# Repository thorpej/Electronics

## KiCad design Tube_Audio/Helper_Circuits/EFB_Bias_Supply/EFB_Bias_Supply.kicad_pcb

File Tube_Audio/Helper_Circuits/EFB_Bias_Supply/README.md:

# EFB(tm) Bias Supply

## EFB(tm) - Enhanced Fixed Bias(tm)

This is a negative bias supply and regulator circuit for use in push-pull Class AB1 fixed bias output
stages of a tube power amplifier.  It is an adaptation of the "EFB II" circuit, developed by
David Gillespie and documented in this thread on AudioKarma: [Improving the Fisher SA-100 with EFB II](http://audiokarma.org/forums/index.php?threads/improving-the-fisher-sa-100-with-efb-ii.476431/).
The idea behind "EFB II" is to maintain the optimum relationship between the negative bias
voltage applied to the tube grids and a reference voltage (the screen supply voltage in a pentode
output stage; the plate supply voltage in an ultra-linear or triode output stage) at any power output
conditions, up to the maximum power the output stage is capable of delivering.  When the
reference voltage sags during, for example, maximum output conditions, the bias voltage will be
reduced (made less negative) proportionally to the change in reference voltage in order to maintain
the desired operating point (avoid an over-bias condition).  This leads to improved performance
(higher power output with less distortion) while also frequently leading to improved tube life
(because the output stage does not need to be under-biased in order to achieve maximum
performance under maximum power conditions).

David's circuit is very clever: a current is passed from the voltage reference through a sense
resistor.  This current produces a voltage drop across another resistor (or resistor network).
This voltage drop is inverted and buffered by a pair of PNP transistors that drive the bias
adjustment and balance network that is tied to the output tube grids.  Any change in the reference
voltage (up or down) results in a change in the sense current, resulting in a proportional change
in the voltage drop across the resistor(s) that set the base bias voltage.

This board is intended to more or less fully encapsulate a bias supply; it contains a half-wave
rectifier and two filter capacitors, in addition to the "EFB II" circuitry.  To use it, simply determine
what your "raw bias voltage" should be, plug in a few values into a handy spreadsheet I've
provided, and then install the calculated components onto the board, *et viola*!  It's tailored for
your particular application.

## Parts you'll need to build your EFB(tm) Bias Supply board

There are a few specific components required to properly assemble your EFB(tm) Bias Supply board.

* A PCB-mounted 50K linear trim pot, TE 409HA503M or equivalent.
* A rectangular radial .22µF (220nF) 50V film capacitor, Kemet SMR5224J50J02L16.5 or equivalent.
* A radial 100µF 250V electrolytic capacitor, 7.5mm lead spacing, up to 16.0mm diameter, Panasonic EEU-ED2E101 or equivalent.
* A radial 47µF 250V electrolytic capacitor, 5.0mm lead spacing, up to 12.5mm diameter, Panasonic EEU-ED2E470 or equivalent.

(All of the above mentioned parts are available from Mouser.)

You will also need:

* 2x 1N4007 diodes.
* 2x KSA1013 or equivalent PNP transistors in TO-92 packages, ECB pin configuration.

...plus a handful of resistors (see the following section about configuring the board), and optional
screw terminal blocks (you can opt to use flying leads if you wish).

Please note that the KSA1013 has a maximum Vce rating of -160V.  If your application requires
a bias voltage in excess of -70V, the KSA1013 may not be suitable.  If you can find another
PNP transistor with a suitable Vce rating in a TO-92 package with an ECB pin configuration, you
should be able to substitute it.  If there's sufficient interest, I could spin another revision of the
board that uses a different TO-92 pin configuration if a suitable high-voltage ECB transistor
proves elusive.  I chose the KSA1013 because that's what David used originally and the price
is right.  Note that higher-voltage transistors would also require higher-voltage electrolytic
capacitors.

## Configuring the EFB(tm) Bias Supply board

This board is meant to be flexible and configurable to make it easy to adapt to a wide variety
of amplifiier applications.  I've provided a handy EFB(tm) Bias Supply Calculator in the form of an
Excel spreadsheet that makes configuring the board for your application fairly easy.  The calculator
ignores things like diode forward voltage and transistor base-emitter voltage drop, but this has
barely any effect on the results because the voltages used with tube amplifiers are typically
much higher in comparison; these small errors are thus lost in the noise.

[Click here](https://github.com/thorpej/Electronics/blob/master/Tube_Audio/Helper_Circuits/EFB_Bias_Supply/EFB_Bias_Supply_Calculator.xlsx) to download the spreadsheet and get started!

### Step 1

Determine your **Sense_Voltage**.  This is the nominal value you will be using as your
voltage reference for the circuit.  For a pentode output stage, this is the nominal screen grid
voltage.  For an ultra-linear or triode output stage, this is the voltage at the primary center tap
of the output transformer.  In the example spreadsheet, we will use 475V.

Enter the **Sense_Voltage** value into cell *B2* of the spreadsheet.

### Step 2

Determine your **Sense_Resistor** values.  The spreadsheet will suggest values that would
be appropriate for your specified **Sense_Voltage** in rows 5 and 6, along with the voltage
drop across those resistors so that you may select resistors with the appropriate voltage rating.
Select the nearest standard values with a 5% tolerance or better whose sum is reasonably close
to the target value in row 7.  A provision for two resistors is provided specifically in order to avoid
exceeding voltage ratings.  If you can safely use a single resistor, then use 0 for one of the resistor
values (and solder a wire jumper on the board in that location).

Enter your **Sense_Resistor** values into cells *B10* and *B11*.

The actual **Sense_Current** that will be generated in the circuit will be shown in cell
*H12*.  It should be reasonably close to 0.75mA (.00075A).

### Step 3

Determine your target **Raw\_Bias\_Voltage**.

The negative voltage produced by the EFB(tm) Bias Supply is not the voltage that will be directly
applied to the grids of the output tubes.  You will want some headroom to adjust up and down
from the nominal value that's appropriate for your application.  Let's say you have an output
stage design that calls for a -35V bias voltage; you might want to have that be the center of a
range that can swing as much as 15% in either direction (from -40.25V to -29.75V).  To get that
range, you're going to be feeding the "raw bias voltage" from the bias supply though a voltage
divider network (maybe individual bias pots for each output tube, or maybe a bias pot combined
with a balance pot for each push-pull pair).  In any case, to provide that -35V +/- 15% range,
you may need as much as -45V to -55V of "raw bias voltage".  Spend some time experimenting
with the included LTSpice simulations of bias / balance networks to determine the appropriate
raw bias voltage for your application.  There are two simulations proivided:

* [Individual_Bias_Network.asc](https://github.com/thorpej/Electronics/tree/master/Tube_Audio/Helper_Circuits/EFB_Bias_Supply/Individual_Bias_Network.asc): This is a network topology that provides an individual pot to fine-tune the bias voltage for each output tube.  The voltage ranges from **Raw\_Bias\_Voltage** to a floor as determined by the bottom leg of a voltage divider.
* [Bias_Balance_Network.asc](https://github.com/thorpej/Electronics/tree/master/Tube_Audio/Helper_Circuits/EFB_Bias_Supply/Bias_Balance_Network.asc): This is a network topology that provides a DC-balance pot and a bias adjustment pot for each push-pull pair of output tubes.  It is more complex to build (my handy [helper board](https://github.com/thorpej/Electronics/tree/master/Tube_Audio/Helper_Circuits/Bias_Balance_Helper_x2) makes it a little easier) and calculate the required resistor values, but it makes DC-balance adjustment somewhat easier because the balance pot adjusts 2 tubes at the same time.  This network requires a more-negative **Raw\_Bias\_Voltage**, as voltage at the outputs of the network is always less negative than **Raw\_Bias\_Voltage**.

Enter the **Raw\_Bias\_Voltage** into cell *B16*.

### Step 4

Determine your **Bias\_Set\_Resistor** value.  The spreadsheet will suggest a value that would
be appropriate for your specified **Raw\_Bias\_Voltage** that would allow the bias adjust pot
to be roughly centered.  Select the nearest standard value with a 5% tolerance or better.

Enter the **Bias\_Set\_Resistor** value into cell *B20*.

### Step 5

Determine your **Bias\_Balance\_Network\_Resistance** value.  This is the effective resistance
to ground of the bias / balance adjuster network (resistors and potentiometers).  Calculate this
with alll of the network's potentiometers centered to determine the nominal value.  Note that
several portions of your network may be in parallel to one another, and that you may need to
account for multiple instances of the network if your amplifier has more than one channel.  If you
have trouble calculating this manually, a great way to determine this reliabily is to simulate your
bias / balance circuit in LTSpice, measure the current flowing through the circuit in simulation,
and use Ohm's Law to calculate the resistance.

Enter the **Bias\_Balance\_Network\_Resistance** value in cell *B33*.

### Step 6

Determine your **auxillary bias supply current**, if any.  This is applicable if you are using the
**Vneg** terminal on the board to provide a voltage source for e.g. a long-tail pair tail circuit.

Enter the **auxillary bias supply current** value in cell *B38*.  If your application does not use
this feature of the board, enter the value 0.

### Step 7

Determine the AC voltage of your bias supply transformer secondary winding.  This is used to
estimate the **Raw\_Neg\_Voltage** that will be present at the bias supply rectifier and first
filter cap.  This is merely an estimate; it's always better to measure, but this estimate is a reasonable
approximation.

Enter the bias transfomer AC voltage in cell *B41*.

Whether you use the estimate or measure, enter the **Raw\_Neg\_Voltage** in cell *B47*.
Note that this voltage is also present at the **Vneg** terminal (see discussion in Step 6).

### Step 8

Determine your **Qpoint\_Dropping\_Resistor** value.  This resistor will drop the **Raw\_Neg\_Voltage**
to the quiescent **Qpoint_Voltage**, which should be roughly double the **Raw\_Bias\_Voltage**
in order to provide even voltage swing on either side of the **Raw\_Bias\_Voltage**.

The target Qpoint voltage drop is calculated by the spreadsheep and reported in cell *H46*.
A target resistor value is suggested by the spreadsheet in cell *H51*.  Select the nearest standard
value with a 5% tolerance or better.

Enter the **Qpoint\_Dropping\_Resistor** value in cell *B56*.

### Step 9

Determine your **Inverter\_Current\_Set\_Resistor** value.  This resistor will set the current of
the inverter transistor (Q1) based on the difference between **Qpoint_Voltage** and
**Raw\_Bias\_Voltage**.  The target current is 1.5mA (0.0015A).  The spreadsheet will suggest
a resistor value in row 60.  Select the nearest standard value with a 5% tolerance or better.

Enter the **Inverter\_Current\_Set\_Resistor** value in cell *B65*.  The resulting current calculated
by the spreadsheet will be displayed in cell *H64*, and should be reasonably close to 1.5mA.

### Step 10

It's time to install parts onto the board!  The spreadsheet will provide resistor values for
R1, R2, R3, R4, and R5 in rows 70-74.  The spreadsheet will also provide the initial bias adjuster
pot setting in row 77.

## Acknowledgements

EFB(tm) and Enhanced Fixed Bias(tm) are trademarks of D Gillespie Designs, and are used with
permission.  Circuit is copyright D Gillespie Designs, and is used with permission.

Please let me know if you find this useful.  Thanks to Kevin Ward for reviewing this content and
providing several helpful suggestions.  And many thanks to David Gillespie for sharing this circuit
with the tube audio community.  Check out his work at [Tronola](http://www.tronola.com/html/dave_s_lab.html).

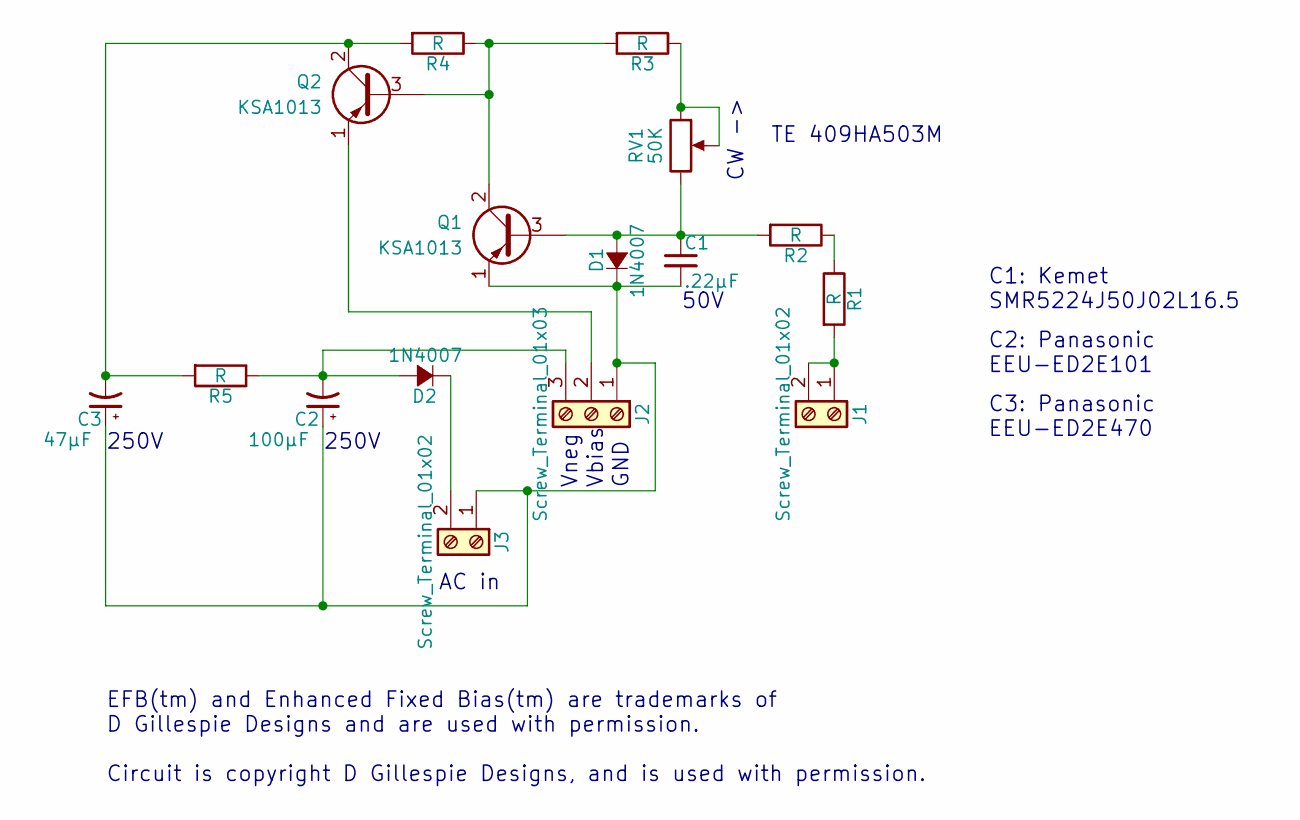
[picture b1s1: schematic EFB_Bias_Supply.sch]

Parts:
C1: .22µF; C_Rect_L7.2mm_W3.5mm_P5.00mm_FKS2_FKP2_MKS2_MKP2
C2: 100µF; CP_Radial_D16.0mm_P7.50mm
C3: 47µF; CP_Radial_D12.5mm_P5.00mm
D1, D2: 1N4007; D_DO-35_SOD27_P7.62mm_Horizontal
J1, J3: Screw_Terminal_01x02; TerminalBlock_bornier-2_P5.08mm
J2: Screw_Terminal_01x03; TerminalBlock_bornier-3_P5.08mm
Q1, Q2: KSA1013; TO-92_Inline_Wide
R1, R2, R3, R4, R5: R; R_Axial_DIN0411_L9.9mm_D3.6mm_P15.24mm_Horizontal
RV1: 50K; Potentiometer_Trimmer_ACP_CA9v_Horizontal_Px10.0mm_Py5.0mm

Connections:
unnamed: C1.1, D1.2 (A), Q1.3 (B), R2.2, RV1.3
unnamed: C1.2, C2.1, C3.1, D1.1 (K), J2.1, J3.1, Q1.1 (E)
unnamed: C2.2, D2.2 (A), J2.3, R5.1
unnamed: C3.2, Q2.2 (C), R4.2, R5.2
unnamed: D2.1 (K), J3.2
unnamed: J1.1, J1.2, R1.2
unnamed: J2.2, Q2.1 (E)
unnamed: Q1.2 (C), Q2.3 (B), R3.2, R4.1
unnamed: R1.1, R2.1
unnamed: R3.1, RV1.1, RV1.2

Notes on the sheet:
CW ->
GND
Vbias
Vneg
AC in
250V
C2: Panasonic EEU-ED2E101
50V
C1: Kemet SMR5224J50J02L16.5
C3: Panasonic EEU-ED2E470
TE 409HA503M
EFB(tm) and Enhanced Fixed Bias(tm) are trademarks of D Gillespie Designs and are used with permission. Circuit is copyright D Gillespie Designs, and is used with permission.

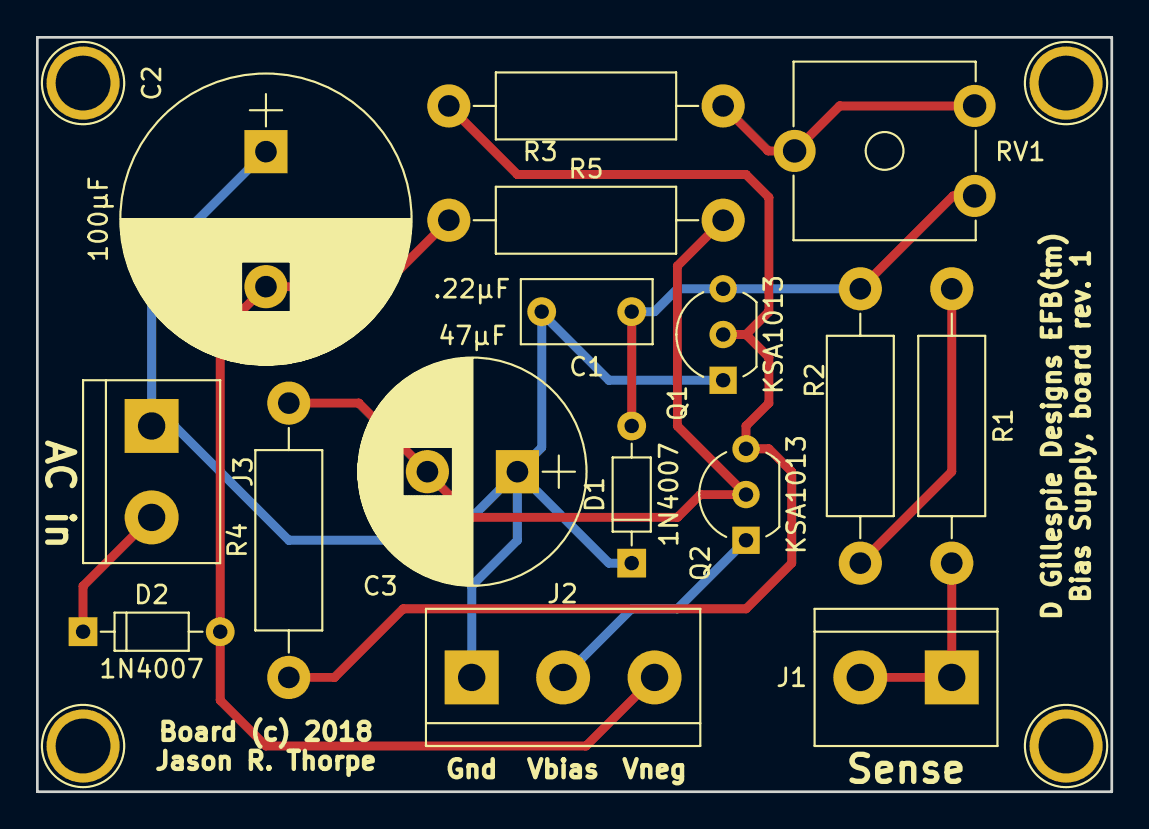
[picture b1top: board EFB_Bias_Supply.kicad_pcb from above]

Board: 2 copper layers, 59.7 x 41.9 mm, 16 parts (0 on the bottom side), 10 nets.

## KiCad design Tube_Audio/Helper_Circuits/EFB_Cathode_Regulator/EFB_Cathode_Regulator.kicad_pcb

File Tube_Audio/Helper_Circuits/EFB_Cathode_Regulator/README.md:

# EFB(tm) Cathode Regulator

## EFB(tm) - Enhanced Fixed Bias(tm)

This is a regulator circuit developed by David Gillespie for generating a fixed cathode bias in the
output stage of a tube power amplifier.  Unlike traditional cathode bias setups, which derive the
bias voltage from the current flowing through the output stage, this cathode regulator maintains
a fixed positive bias voltage on the output tube cathodes regardless of the current flowing through
the tubes.  This prevents an over-bias condition when the tubes are driven to full power, increasing
power output and reducing distortion.

In addition to maintaining a fixed bias voltage, the regulator is referenced to the output stage's
screen voltage (for pentode mode) or the plate voltage (for ultra-linear mode).  If the power supply
sags for some reason, the regulator compensates by reducing the bias applied to the cathodes,
thus maintaining the optimal operating point.  This flavor of EFB(tm) is best suited for smaller power
amplifiers, such as those based on the 6V6 or EL84/6BQ5.

The circuit is very simple.  It is comprised of an adjustable voltage divider and an LM337 negative
voltage regulator, along with some ancillary compomnents for stability and current sensing.   The
voltage regulator is made up of a large dropping resistor (330K 2W is a common value), a trim pot
(typically 10K), and a tail resistor valued to suit the desired voltage range.  The voltage divider takes
the reference voltage and outputs a voltage that is fed to the adjusment pin of the LM337, which is
stabilized by a 4.7µF capacitor.  The LM337 will output a voltage approximately 1.25V lower than the
adjustment pin voltage.  The output pin of the LM337 is connected to the cathodes of the output
stage through a 10R 1% 2W resistor used for current sensing, allowing easy measurement of
the total output stage quiescent current.  There is a 22µF capacitor connected to the LM337 output
pin to provide AC bypass of the output tube cathodes.The input pin of the LM337 is connected to
ground.  The total cathode current of the output stage flows through the LM337 to ground.

Because the LM337 input is connected to ground, the LM337 itself can be used to connect the
regulator board to the amplifier chassis.  The trim pot should be oriented so that bias can be
adjusted while the regulator board is mounted to the chassis.  The chassis sinks any heat
generated by the LM337.

I have spec'd the large voltage divider leg as 2W as a safety margin; a 1W resistor is probably
sufficient, but I personally prefer to use a 2W part there.  The trim pot and lower divider leg can
be 1/2W parts.  The current sensing resistor should be a 10R 2W 1% part for accuracy.  The
4.7µF and 22µF capacitors should be rated for 50V.  I prefer to use long-life Nichicon electrolytics
here.  If you want to skip the current sensing capability, you need to install a wire jumper in lieu
of the 10R resistor.  Any decent quality LM337 should work fine.  The TI and ST versions are great.
I have a bag of Fairchild parts that work perfectly well.

## Acknowledgements

EFB(tm) and Enhanced Fixed Bias(tm) are trademarks of D Gillespie Designs, and are used with
permission.  Circuit is copyright D Gillespie Designs, and is used with permission.

Please let me know if you find this useful.  And many thanks to David Gillespie for sharing this
circuit with the tube audio community.  Check out his work at [Tronola](http://www.tronola.com/html/dave_s_lab.html).

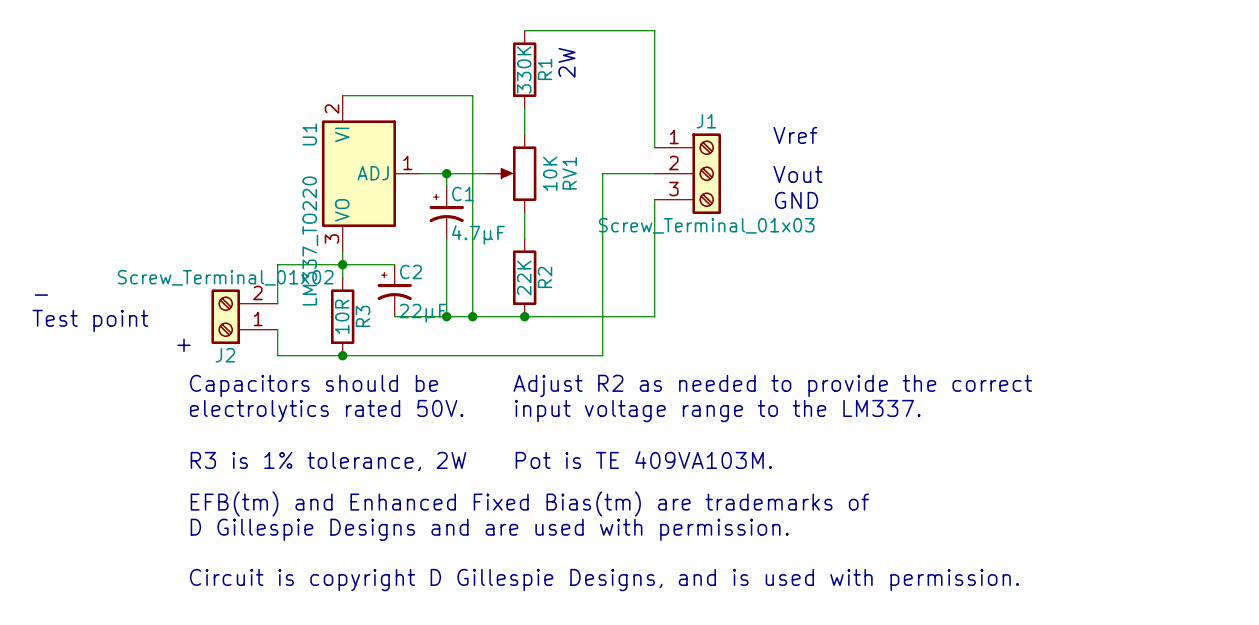
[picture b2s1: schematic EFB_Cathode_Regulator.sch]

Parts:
C1: 4.7µF; CP_Radial_D5.0mm_P2.00mm
C2: 22µF; CP_Radial_D6.3mm_P2.50mm
J1: Screw_Terminal_01x03; TerminalBlock_bornier-3_P5.08mm
J2: Screw_Terminal_01x02; TerminalBlock_bornier-2_P5.08mm
R1: 330K; R_Axial_DIN0414_L11.9mm_D4.5mm_P15.24mm_Horizontal
R2: 22K; R_Axial_DIN0309_L9.0mm_D3.2mm_P12.70mm_Horizontal
R3: 10R; R_Axial_DIN0411_L9.9mm_D3.6mm_P12.70mm_Horizontal
RV1: 10K; Potentiometer_Trimmer_Piher_PT-10h2.5_Vertical_Px2.5mm_Py5.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
U1: LM337_TO220; TO-220-3_Vertical

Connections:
unnamed: C1.1, RV1.2, U1.1 (ADJ)
unnamed: C1.2, C2.2, J1.3, R2.2, U1.2 (VI)
unnamed: C2.1, J2.2, R3.1, U1.3 (VO)
unnamed: J1.1, R1.1
unnamed: J1.2, J2.1, R3.2
unnamed: R1.2, RV1.1
unnamed: R2.1, RV1.3

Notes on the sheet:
Vref
Vout
GND
- Test point +
Adjust R2 as needed to provide the correct input voltage range to the LM337.
Capacitors should be electrolytics rated 50V.
Pot is TE 409VA103M.
R3 is 1% tolerance, 2W
EFB(tm) and Enhanced Fixed Bias(tm) are trademarks of D Gillespie Designs and are used with permission. Circuit is copyright D Gillespie Designs, and is used with permission.

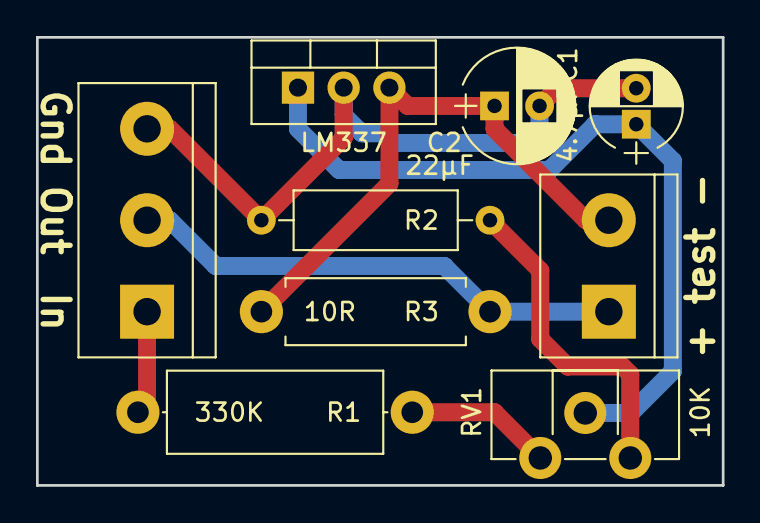
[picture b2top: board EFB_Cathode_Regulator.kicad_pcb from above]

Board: 2 copper layers, 38.1 x 24.9 mm, 9 parts (0 on the bottom side), 7 nets.

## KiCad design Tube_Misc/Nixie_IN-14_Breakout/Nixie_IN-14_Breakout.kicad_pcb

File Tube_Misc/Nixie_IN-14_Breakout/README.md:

# IN-14 Nixie Tube Breakout Board

This is just a simple breakout board to make it easier to play around with IN-14 Nixie tubes
(or any other Nixie that uses the same basic footprint); I included some old Soviet iconography
on the board just for fun.

To use the board, thread the spindly IN-14 lead wires through the holes and solder it into place.
The arrow on the footprint indicates the anode lead wire, and corresponds to the arrow on the bottom
of the glass.  The R1 resistor footprint is for the required current-limiting resistor.  If your power
supply is already current-limited, yoiu can just place a jumper in this position.  Attach some standard
5.04mm pitch screw terminals and some standoffs with #4 machine screws and you're all set.

## Current-limiting Resistor Selection

Nixie tubes work like a neon bulb: a threshold voltage is required to light them up (the "striking"
voltage), and until that threshold is reached, they behave like an open circuit.  However, once the
gas ionizes and the glow discharge begins, the resistance drops very quickly to the low-1000s of Ohms.
In order to avoid destroying the tube, the current must be limited.  For IN-14s, the maximum allowable
current is 2.5mA for the digits (and quite a bit less for the decimal points; on the order of 0.5mA).

A fairly safe way to determine the initial value for your current limiting resistor is to use Ohm's Law
to calculate the resistor needed to drop the supply voltage at the max current.  So, if you have a 180V
supply, and wish to limit to 2.5mA, you would need a 72K resistor; 75K is close enough.  It's done this
way to guarantee that you will not exceed the max current through the tube.  The actual current drawn
in the next step will be significantly less than 2.5mA because there will be some voltage dropped across
the tube.

Now, hook up your Nixie with this resistor in-series with the anode and connect one of the cathodes to
ground, let the digit light up, and measure the voltage drop across the resistor.  For this example, we'll
say that 49V is dropped across the resistor.  Ths means that 0.7mA is flowing through the tube.  Now use
Ohm's law again to calculate a new resistor value to give you the desired current at the voltage drop
that you just measured.  In this case, I want 1mA to flow through my Nixies, which would mean a 49K resistor;
47K is the closest standard value which is what I'll use.  1/2W rating will be sufficient.  If you want
2.5mA to flow, a 22K resistor will get you close enough; I chose 1mA because I can't tell any difference
in brightness, and 1mA gives me plenty of safety margin and should extend the life of the tube.

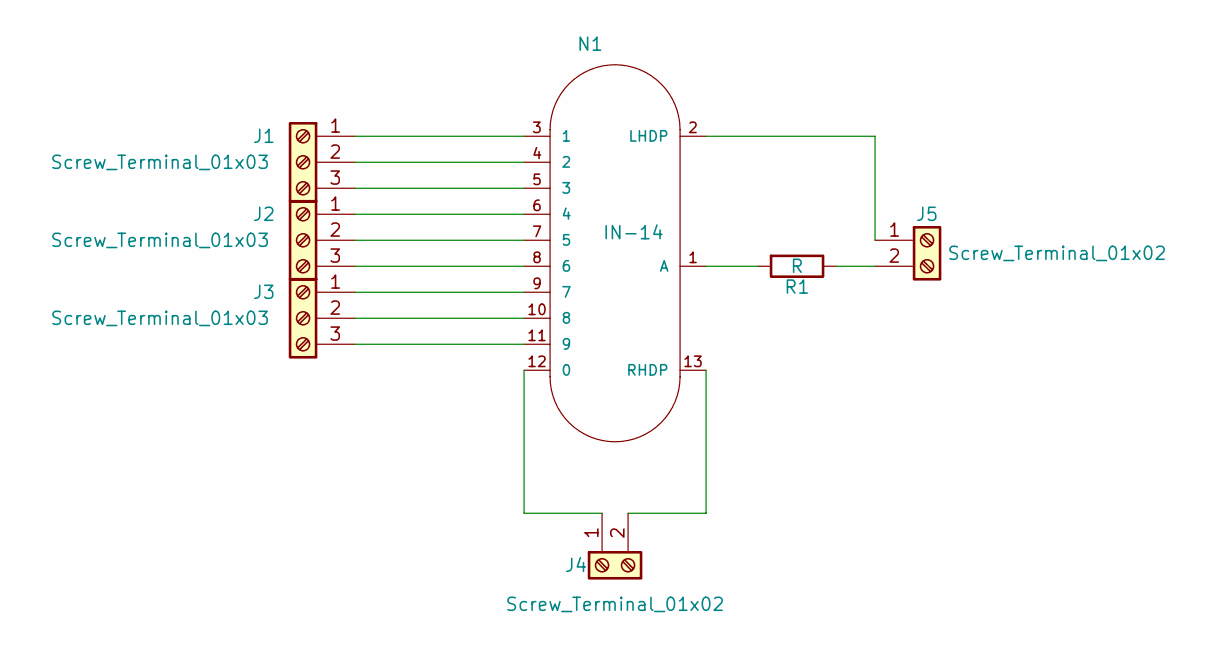
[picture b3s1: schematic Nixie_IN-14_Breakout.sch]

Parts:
J1, J2, J3: Screw_Terminal_01x03; TerminalBlock_bornier-3_P5.08mm
J4, J5: Screw_Terminal_01x02; TerminalBlock_bornier-2_P5.08mm
N1: IN-14; Nixie-IN-14
R1: R; R_Axial_DIN0414_L11.9mm_D4.5mm_P15.24mm_Horizontal

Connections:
unnamed: J1.1, N1.3 (1)
unnamed: J1.2, N1.4 (2)
unnamed: J1.3, N1.5 (3)
unnamed: J2.1, N1.6 (4)
unnamed: J2.2, N1.7 (5)
unnamed: J2.3, N1.8 (6)
unnamed: J3.1, N1.9 (7)
unnamed: J3.2, N1.10 (8)
unnamed: J3.3, N1.11 (9)
unnamed: J4.1, N1.12 (0)
unnamed: J4.2, N1.13 (RHDP)
unnamed: J5.1, N1.2 (LHDP)
unnamed: J5.2, R1.1
unnamed: N1.1 (A), R1.2

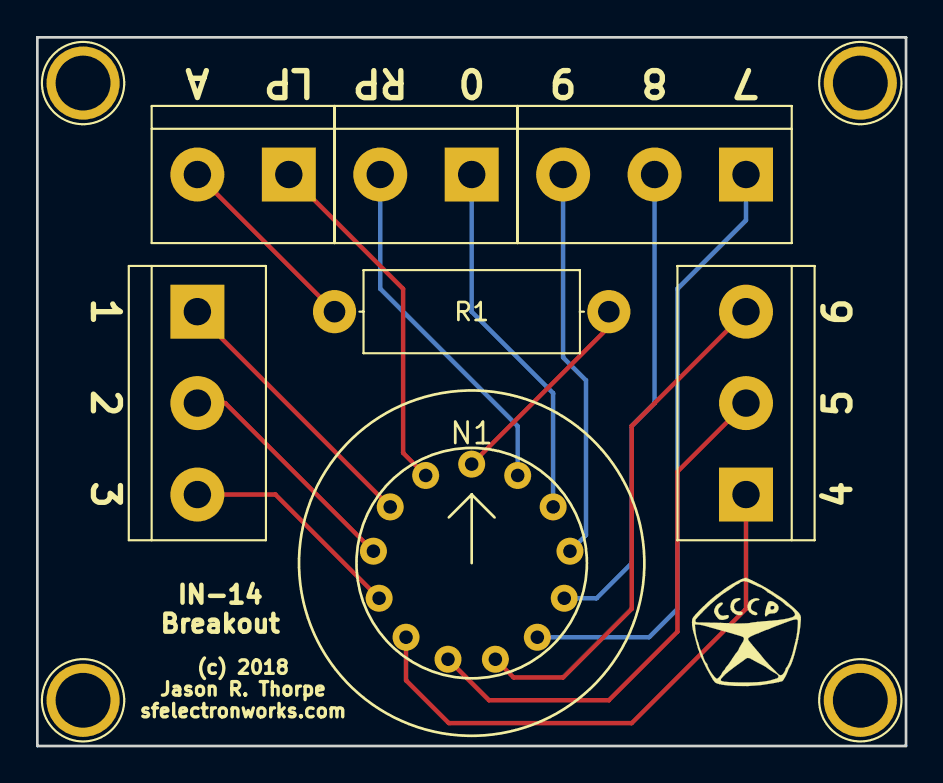
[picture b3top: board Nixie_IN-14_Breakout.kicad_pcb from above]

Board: 2 copper layers, 48.3 x 39.4 mm, 7 parts (0 on the bottom side), 14 nets.

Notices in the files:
Tube_Audio/Helper_Circuits/EFB_Bias_Supply/EFB_Bias_Supply.kicad_pcb:
Board (c) 2018
Tube_Audio/Helper_Circuits/EFB_Cathode_Regulator/EFB_Cathode_Regulator.kicad_pcb:
Board (c) 2018 Jason R. Thorpe.
Tube_Misc/Nixie_IN-14_Breakout/Nixie_IN-14_Breakout.kicad_pcb:
(c) 2018
